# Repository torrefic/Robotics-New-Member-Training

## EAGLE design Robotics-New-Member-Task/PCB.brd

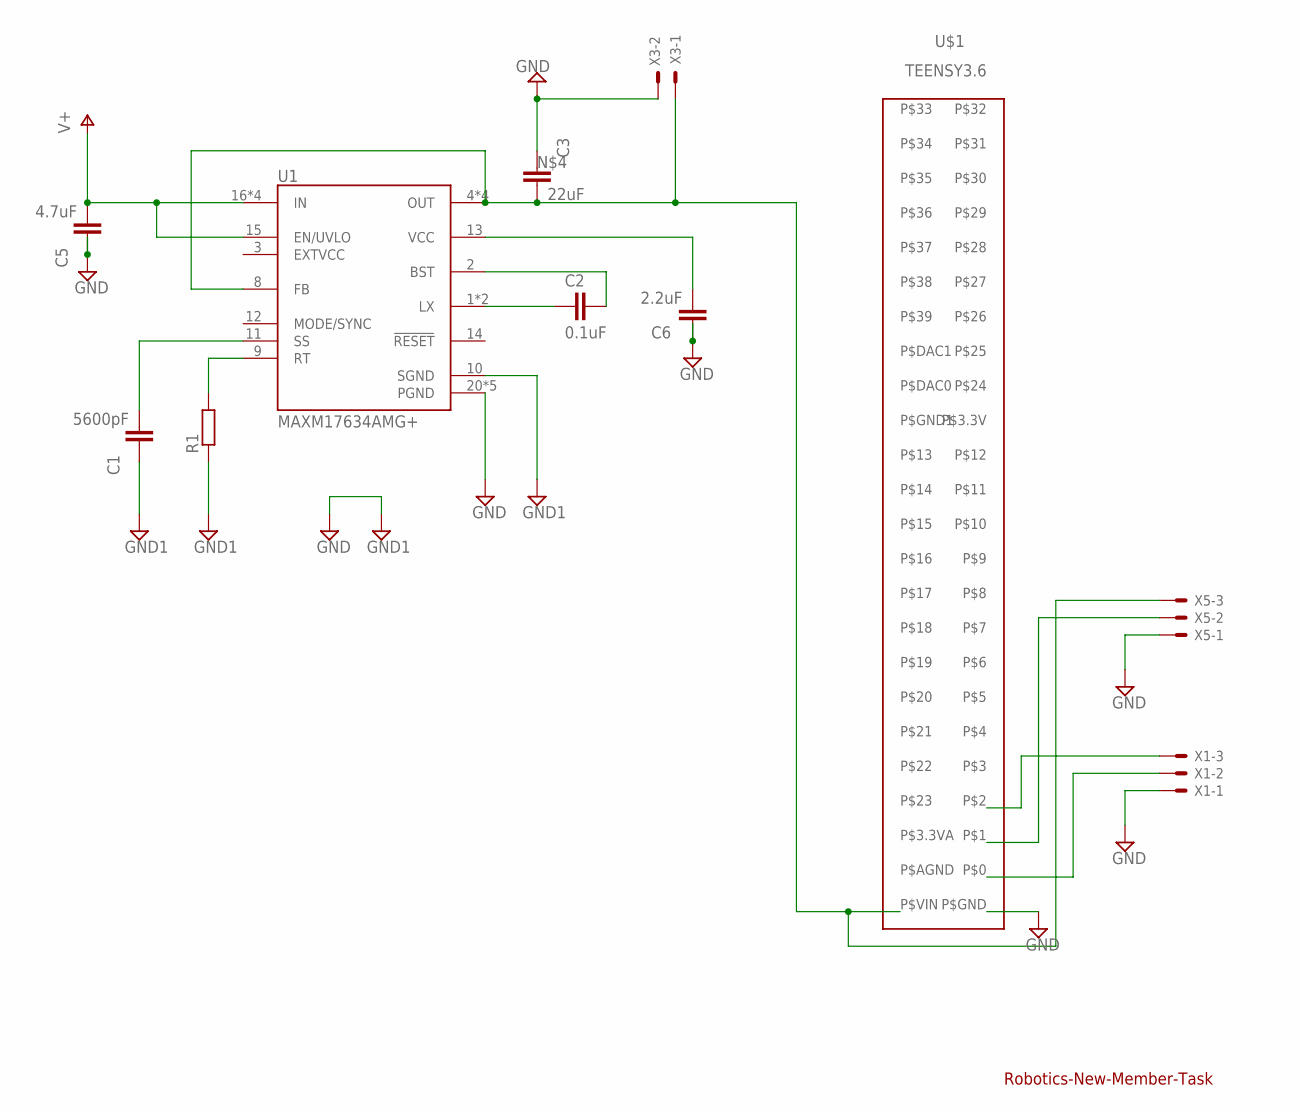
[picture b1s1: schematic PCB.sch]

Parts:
C1: 5600pF; C0805
C2: 0.1uF; C0805
C3: 22uF; C0805
C5: 4.7uF; C0805
C6: 2.2uF; C0805
R1: R-EU_R0805; R0805
U1: MAXM17634AMG+; QFN50P400X400X180-25N
U$1: TEENSY3.6
X1, X5: KK-156-3
X3: KK-156-2

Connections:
GND: C3.1, C5.1, C6.1, U1.20 (PGND), U1.21 (PGND), U1.22 (PGND), U1.23 (PGND), U1.25 (PGND), U$1.P$GND, X1.1, X3.2, X5.1
GND1: C1.1, R1.1, U1.10 (SGND)
unnamed: C6.2, U1.13 (VCC)
unnamed: R1.2, U1.9 (RT)
unnamed: C1.2, U1.11 (SS)
unnamed: C3.2, U1.4 (OUT), U1.5 (OUT), U1.6 (OUT), U1.7 (OUT), U1.8 (FB), U$1.P$VIN, X3.1, X5.3
unnamed: C2.1, U1.2 (BST)
unnamed: C2.2, U1.1 (LX), U1.24 (LX)
unnamed: U$1.P$0, X1.2
unnamed: U$1.P$1, X5.2
unnamed: U$1.P$2, X1.3
V+: C5.2, U1.15 (EN/UVLO), U1.16 (IN), U1.17 (IN), U1.18 (IN), U1.19 (IN)

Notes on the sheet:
Robotics-New-Member-Task

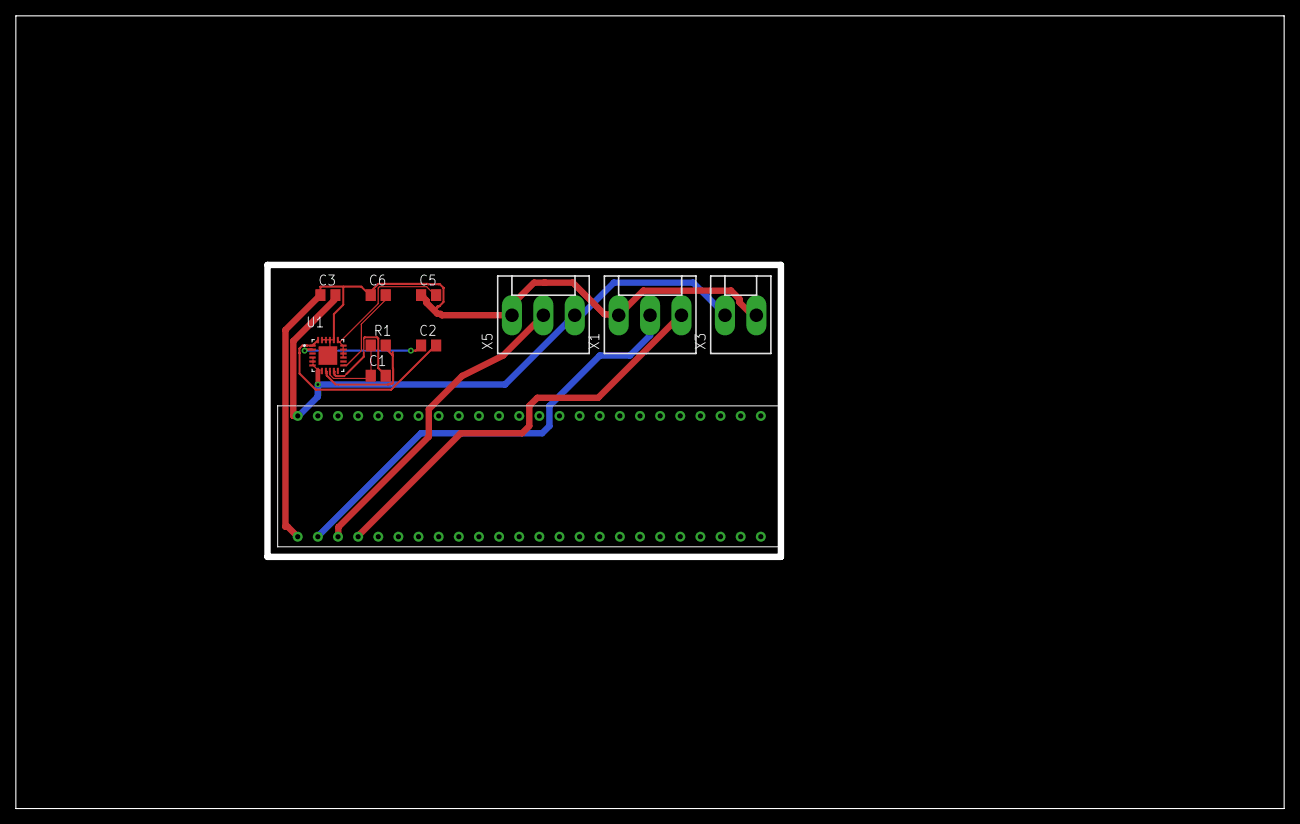
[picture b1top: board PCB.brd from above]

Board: 2 copper layers, 160.0 x 100.0 mm, 11 parts (0 on the bottom side), 12 nets.

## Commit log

2021-02-04 Finished training
